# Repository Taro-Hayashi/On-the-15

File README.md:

# On the 15 ビルドガイド（[English](README_EN.md)）
- [キット内容](#キット内容)
- [レイアウトを決める](#レイアウトを決める)
- [はんだ付け](#はんだ付け)
- [組み立て](#組み立て)
- [キーのカスタマイズ](#キーのカスタマイズ)
- [そのほか](#そのほか)

## キット内容

||部品名|数|
|-|-|-|
|1|メインボード|1|
|2|トッププレート|1|
|3|ボトムプレート|1|
|4|ネジ|22|
|5|スペーサー|11|
|6|リセットスイッチ|1|
|7|Cherry MX ホットスワップソケット|60|
|8|ゴム足|6|
|9|アクリルミドルプレート||
|10|2Uスタビライザー|1|
|11|ロータリーエンコーダー|1|
|12|ノブ|1|

### キット以外に必要なもの
|部品名|数|||
|-|-|-|-|
|キースイッチ|〜60|CherryMX互換|[遊舎工房](https://shop.yushakobo.jp/collections/all-switches/cherry-mx-%E4%BA%92%E6%8F%9B-%E3%82%B9%E3%82%A4%E3%83%83%E3%83%81) / [TALPKEYBOARD](https://talpkeyboard.net/?category_id=59cf8860ed05e668db003f5d) / [DailyCraftKeyboard](https://shop.dailycraft.jp/collections/mx-switches)|
|キーキャップ|〜60|CherryMX互換|[遊舎工房](https://shop.yushakobo.jp/collections/keycaps/cherry-mx-%E4%BA%92%E6%8F%9B-%E3%82%AD%E3%83%BC%E3%82%AD%E3%83%A3%E3%83%83%E3%83%97) / [TALPKEYBOARD](https://talpkeyboard.net/?category_id=59e2acfaed05e644fd004008)|
|Type-C ケーブル|1|||

### 追加できるもの
|部品名|||
|-|-|-|
|色違いアクリルプレート|-|[遊舎工房 - キーボードアクリルプレート](https://shop.yushakobo.jp/collections/services/products/keyboard_acrylic_plate?variant=43949129629927)|
|スタビライザー|2U、PCBマウント|[遊舎工房](https://shop.yushakobo.jp/collections/all-keyboard-parts/Stabilizer) / [TALPKEYBOARD](https://talpkeyboard.net/?category_id=5f884b9b3313d216eb50558a)|
|ロータリーエンコーダ|EC11/EC12/ロープロファイル|[遊舎工房](https://shop.yushakobo.jp/search?q=%E3%83%AD%E3%83%BC%E3%82%BF%E3%83%AA%E3%83%BC%E3%82%A8%E3%83%B3%E3%82%B3%E3%83%BC%E3%83%80%E3%83%BC+%E3%83%8E%E3%83%96%E4%BB%98%E3%81%8D) / [TALPKEYBOARD](https://talpkeyboard.net/items/5f3f1a597df28129f2fd4b0f) / [DailyCraftKeyboard](https://shop.dailycraft.jp/products/encoder_low)|
|ノブ|外径19mmまで|[遊舎工房](https://shop.yushakobo.jp/products/3733) / [DailyCraftKeyboard](https://shop.dailycraft.jp/products/encoder_lowprofile_knob)|

専用のアクリルケースもあります。  
- [アクリルケースデータ](acrylic-case/README.md)
  - [fully-acrylic](acrylic-case/fully-acrylic/README.md)
  - [pcb-switchplate](acrylic-case/pcb-switchplate/README.md)

### 必要な工具
|工具名|
|-|
|はんだごて|
|こて先クリーナー（こて台）|
|鉛入りはんだ|
|ピンセット|
|精密ドライバー|

## レイアウトを決める
On the 15は60キーの格子配列キーボードですが、色のついたキーは長さを変更することができます。  

ビルドガイドではこのようなレイアウトで組み立てます。　

## はんだ付け
### ソケットのはんだ付け
使うソケットのパッドに予備はんだをします。  
あらかじめ薄くはんだを乗せます。  
  
ソケットを置いたらピンセットで押さえつけながらはんだを注いでいきます。入り組んでいて表面積が多いので多めに必要になります。

慣れてきたら予備はんだを省略したり、一度に複数個置いてはんだ付けをすると楽になります。  
  
### リセットスイッチのはんだ付け
表面左側のRESETと書いてあるところにリセットスイッチを差して裏からはんだ付けします。  

### ロータリーエンコーダーのはんだ付け
足を折らないようにホールに通して裏からはんだ付けします。  

### テストファームウェアの書き込み
テスト用のファームウェアをこちらからダウンロードしてください。
- https://remap-keys.app/catalog/9bQPDxdkX8xgflHlsR9p/firmware

QMK Toolboxのreleaseページから最新版をダウンロードしてインストールください。  
- [Releases・qmk/qmk_toolbox](https://github.com/qmk/qmk_toolbox/releases)

起動したらOpenを押してダウンロードしたファームウェアを指定し、はんだ付けしたリセットボタンを押します。  
   
新しく黄色の文字が出てきたらFlashを押します。  

Thank youの後に黄色い文字が出たら更新完了です。  

### 動作確認
キースイッチを差したり裏をピンセットで短絡したりして動作確認をします。  

## 組み立て
### スタビライザーを組み立てる
スタビライザーがあると2Uのキーの押下が安定します。無くても使えるのでお好みでお使いください。  
ねじ止め式のスタビライザーは縦に二つ並べておくことはできないので使う場所に気をつけるかスナップ型のスタビライザーを使ってください。  

小さい方のパーツの穴が二つ開いている側を、大きいパーツの穴が開いている方向に合わせて組み合わせます。  
  
金属の棒を下の穴に差し込みツメにパチっと音がするまで押し込んで完成です。  
    
基板の大きい方の穴にツメをひっかけながら取り付けます。  

### メインボードにトッププレートを取り付ける
トッププレートの裏側にスペーサーをねじ止めします。  
   
メインボードにかぶせて、4隅のスイッチをはめ込みます。  
   
すべてのスイッチを差し込みました。  

### アクリルプレートを挟み込む
画像のような形で3段にして挟み込みます。  

### バックプレートを取り付ける
バックプレートをねじ止めしてゴム足を貼ります。  
  
キーキャップを付けたら完成です。  

### Remap用ファームウェアの書き込み
Remap用のファームウェアをこちらからダウンロードして、さきほどと同様に書き込んでください。
- https://remap-keys.app/catalog/9bQPDxdkX8xgflHlsR9p/firmware

## キーのカスタマイズ
こちらのサイトにアクセスしてください。
- Remap https://remap-keys.app

左を選んで進んでいくとダイアログが出てキーボードを選択できます。  
  
選択して接続してください。

### キーマップの保存と復元
⇔アイコンで作ったキーマップを保存することができます。  
  
作ったキーマップを共有することもできるので是非お試しください。

### レイアウトを変える
キーボードの右のこのボタンでレイアウトを変えることができます。  

### キーを設定する
下のキー一覧からドラッグアンドドロップし、変更が終わったら右上のflashボタンを押すと反映されます。  
  
また、USキーボードとJISキーボードはFlashの下のプルダウンから変更できます。OSの設定に合わせてください。

### 修飾キーとの組み合わせを設定する
上のキーボードのキーをクリックすると設定画面になります。
  
修飾キーと同時押ししたいキーを検索し、同時押ししたい修飾キーにチェックを入れます。

Hold-Tapもここから設定できます。

### ロータリーエンコーダーを設定する
丸いキーの左下をクリックすると時計回り、反時計回りを切り替えることができるので、それぞれにキーを割り当てます。

### 特殊なキーを設定する
FUNCTIONSタブのVIA USER KEYにあらかじめ用意されたショートカットキーがあります。

### LEDを調整する
このボタンで発光方法を変更することができます。

## そのほか
### リセットスイッチの押し方
こちらの隙間からドライバーやピンセットを差し込むことで押すことができます。

### ファームウェアのコード
https://github.com/Taro-Hayashi/qmk_firmware/tree/tarohayashi/keyboards/tarohayashi/onthe15

### プレートのデータ
- [onthe15_plates.zip](https://github.com/Taro-Hayashi/On-the-15/releases/download/0.22.3/onthe15_plates.zip)

### アクリルケースのデータ
- [fully-acrylic](acrylic-case/fully-acrylic/README.md)
- [pcb-switchplate](acrylic-case/pcb-switchplate/README.md)

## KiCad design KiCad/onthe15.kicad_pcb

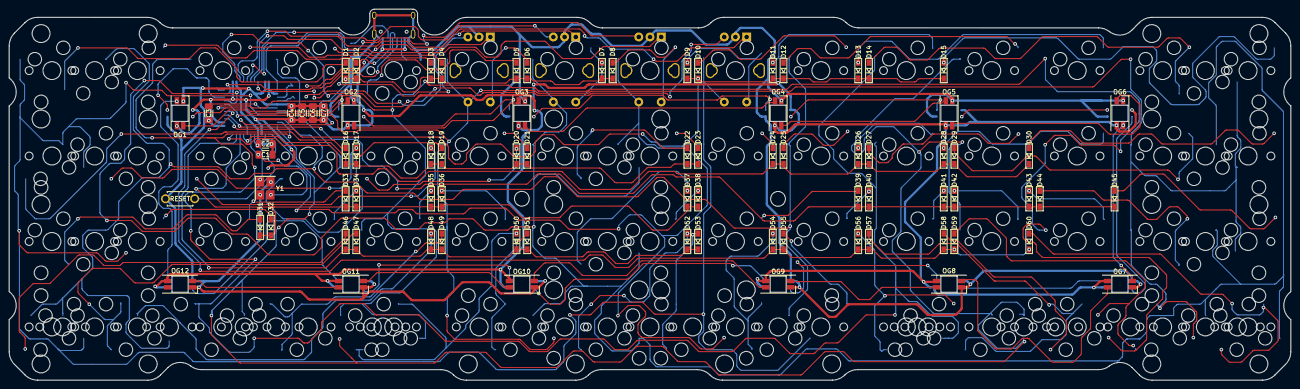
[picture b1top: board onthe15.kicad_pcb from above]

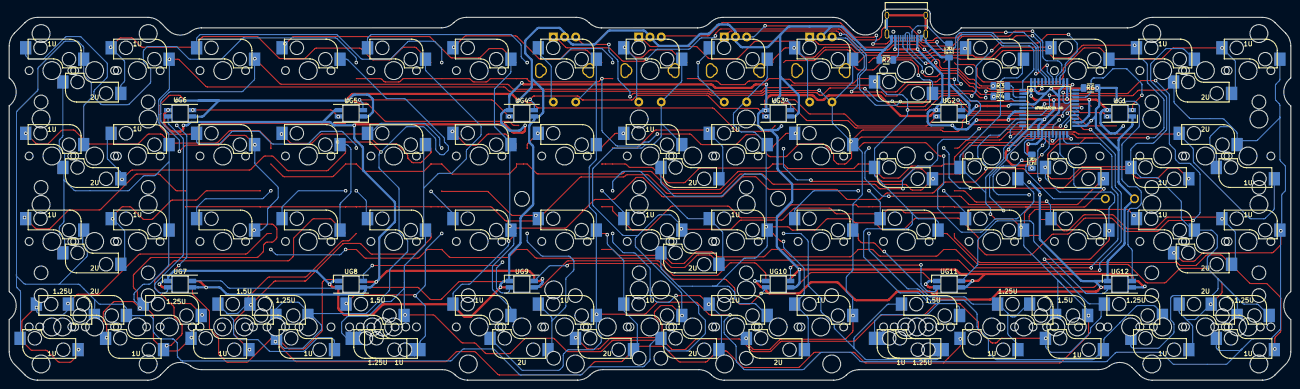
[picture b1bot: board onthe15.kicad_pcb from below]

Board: 2 copper layers, 285.8 x 82.7 mm, 193 parts (20 on the bottom side), 121 nets.

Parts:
C1, C2: 22p; C_1206_3216_SMD
C3: 1u; C_1206_3216_SMD
C4, C5, C6: 0.1u; C_1206_3216_SMD
C7: 10u; C_1206_3216_SMD
D1, D2, D3, D4, D5, D6, D7, D8, D9, D10, D11, D12, D13, D14, D15, D16, D17, D18, D19, D20, D21, D22, D23, D24, D25, D26, D27, D28, D29, D30, D31, D32, D33, D34, D35, D36, D37, D38, D39, D40, D41, D42, D43, D44, D45, D46, D47, D48, D49, D50, D51, D52, D53, D54, D55, D56, D57, D58, D59, D60: D; Diode_SMD
H5, H6: Hole; Hole_3.3mm_Spacer
J1: USB_C_Receptacle_USB2.0
OG1, OG2, OG3, OG4, OG5, OG6, OG7, OG8, OG9, OG10, OG11, OG12: YS-SK6812MINI-E_overglow; YS-SK6812MINI-E_Undergrow_NOHOLE
R1, R2: 5.1k; R_1206_3216_SMD
R3, R4: 22; R_1206_3216_SMD
R5, R6: 10k; R_1206_3216_SMD
RE1, RE2, RE3, RE4: Rotary_Encoder; RotaryEncoder
RST1: ResetSW
SW1, SW2, SW19, SW20, SW36, SW37, SW38, SW62, SW66, SW67, SW71: 2U; MXOnly-2U-FLIPPED-Hotswap-LED
SW3, SW4, SW16, SW17, SW21, SW22, SW27, SW28, SW34, SW35, SW39, SW40, SW45, SW46, SW52, SW53, SW72, SW73, SW74, SW75, SW76, SW77, SW78, SW79, SW80, SW81, SW82, SW83, SW84, SW85, SW86: 1U; MXOnly-1U-Hotswap
SW5, SW6, SW7, SW8, SW9, SW10, SW11, SW12, SW13, SW14, SW15, SW23, SW24, SW25, SW26, SW29, SW30, SW31, SW32, SW33, SW41, SW42, SW43, SW44, SW47, SW48, SW49, SW50, SW51: SW_PUSH; MXOnly-1U-Hotswap
SW18, SW65, SW68: 2U; MXOnly-2U-Hotswap-ReversedStabilizers
SW54, SW56, SW57, SW58, SW59, SW61: 1.25U; MXOnly-1.25U-Hotswap
SW55, SW60: 1.25U; MXOnly-1.25U-Hotswap-Reverse
SW63, SW64, SW69, SW70: 1.5U; MXOnly-1.5U-Hotswap
U1: ATMEGA32U4-AU
UG1, UG2, UG3, UG4, UG5, UG6, UG7, UG8, UG9, UG10, UG11, UG12: YS-SK6812MINI-E_underglow; YS-SK6812MINI-E_Undergrow
Y1: Crystal; Crystal_3225_SMD

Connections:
GND: C1.2, C2.2, C3.2, C4.2, C5.2, C6.2, C7.2, J1.A1 (GND), J1.A12 (GND), J1.B1 (GND), J1.B12 (GND), J1.S1 (SHIELD), OG1.3 (VSS), OG2.3 (VSS), OG3.3 (VSS), OG4.3 (VSS), OG5.3 (VSS), OG6.3 (VSS), OG7.3 (VSS), OG8.3 (VSS), OG9.3 (VSS), OG10.3 (VSS), OG11.3 (VSS), OG12.3 (VSS), R1.2, R2.2, R6.2, RE1.C, RE2.C, RE3.C, RE4.C, RST1.2, U1.5 (UGND), U1.15 (GND), U1.23 (GND), U1.35 (GND), U1.43 (GND), UG1.3 (VSS), UG2.3 (VSS), UG3.3 (VSS), UG4.3 (VSS), UG5.3 (VSS), UG6.3 (VSS), UG7.3 (VSS), UG8.3 (VSS), UG9.3 (VSS), UG10.3 (VSS), UG11.3 (VSS), UG12.3 (VSS), Y1.2, Y1.4
unnamed: C3.1, U1.6 (UCAP)
unnamed: D1.2 (A), SW1.2, SW3.2
unnamed: D2.2 (A), SW4.2
unnamed: D3.2 (A), SW5.2
unnamed: D4.2 (A), SW6.2
unnamed: D5.2 (A), SW7.2
unnamed: D10.2 (A), SW12.2
unnamed: D11.2 (A), SW13.2
unnamed: D12.2 (A), SW14.2
unnamed: D13.2 (A), SW15.2
unnamed: D14.2 (A), SW2.2, SW16.2
unnamed: D15.2 (A), SW17.2
unnamed: D16.2 (A), SW18.2, SW21.2
unnamed: D17.2 (A), SW22.2
unnamed: D18.2 (A), SW23.2
unnamed: D19.2 (A), SW24.2
unnamed: D20.2 (A), SW25.2
unnamed: D21.2 (A), SW26.2
unnamed: D22.2 (A), SW19.2, SW27.2
unnamed: D23.2 (A), SW28.2
unnamed: D24.2 (A), SW29.2
unnamed: D25.2 (A), SW30.2
unnamed: D26.2 (A), SW31.2
unnamed: D27.2 (A), SW32.2
unnamed: D28.2 (A), SW33.2
unnamed: D29.2 (A), SW20.2, SW34.2
unnamed: D30.2 (A), SW35.2
unnamed: D31.2 (A), SW36.2, SW39.2
unnamed: D32.2 (A), SW40.2
unnamed: D33.2 (A), SW41.2
unnamed: D34.2 (A), SW42.2
unnamed: D35.2 (A), SW43.2
unnamed: D36.2 (A), SW44.2
unnamed: D37.2 (A), SW37.2, SW45.2
unnamed: D38.2 (A), SW46.2
unnamed: D39.2 (A), SW47.2
unnamed: D40.2 (A), SW48.2
unnamed: D41.2 (A), SW49.2
unnamed: D42.2 (A), SW50.2
unnamed: D43.2 (A), SW51.2
unnamed: D44.2 (A), SW38.2, SW52.2
unnamed: D45.2 (A), SW53.2
unnamed: D46.2 (A), SW72.2
unnamed: D47.2 (A), SW54.2, SW62.2, SW73.2
unnamed: D48.2 (A), SW55.2, SW74.2
unnamed: D49.2 (A), SW56.2, SW63.2, SW75.2
unnamed: D50.2 (A), SW57.2, SW64.2, SW76.2
unnamed: D51.2 (A), SW65.2, SW77.2
unnamed: D52.2 (A), SW66.2, SW78.2
unnamed: D53.2 (A), SW67.2, SW79.2
unnamed: D54.2 (A), SW68.2, SW80.2
unnamed: D55.2 (A), SW81.2
unnamed: D56.2 (A), SW58.2, SW69.2, SW82.2
unnamed: D57.2 (A), SW59.2, SW70.2, SW83.2
unnamed: D58.2 (A), SW84.2
unnamed: D59.2 (A), SW60.2, SW85.2
unnamed: D60.2 (A), SW61.2, SW71.2, SW86.2
unnamed: J1.A5 (CC1), R1.1
unnamed: J1.A6 (D+), J1.B6 (D+), R4.2
unnamed: J1.A7 (D-), J1.B7 (D-), R3.2
unnamed: J1.B5 (CC2), R2.1
unnamed: OG1.2 (DOUT), OG2.4 (DIN)
unnamed: OG1.4 (DIN), UG12.2 (DOUT)
unnamed: OG2.2 (DOUT), OG3.4 (DIN)
unnamed: OG3.2 (DOUT), OG4.4 (DIN)
unnamed: OG4.2 (DOUT), OG5.4 (DIN)
unnamed: OG5.2 (DOUT), OG6.4 (DIN)
unnamed: OG6.2 (DOUT), OG7.4 (DIN)
unnamed: OG7.2 (DOUT), OG8.4 (DIN)
unnamed: OG8.2 (DOUT), OG9.4 (DIN)
unnamed: OG10.2 (DOUT), OG11.4 (DIN)
unnamed: OG9.2 (DOUT), OG10.4 (DIN)
unnamed: OG11.2 (DOUT), OG12.4 (DIN)
unnamed: R6.1, U1.33 (PE2)
unnamed: UG1.2 (DOUT), UG2.4 (DIN)
unnamed: UG2.2 (DOUT), UG3.4 (DIN)
unnamed: UG3.2 (DOUT), UG4.4 (DIN)
unnamed: UG4.2 (DOUT), UG5.4 (DIN)
unnamed: UG5.2 (DOUT), UG6.4 (DIN)
unnamed: UG6.2 (DOUT), UG7.4 (DIN)
unnamed: UG7.2 (DOUT), UG8.4 (DIN)
unnamed: UG8.2 (DOUT), UG9.4 (DIN)
unnamed: UG10.2 (DOUT), UG11.4 (DIN)
unnamed: UG9.2 (DOUT), UG10.4 (DIN)
unnamed: UG11.2 (DOUT), UG12.4 (DIN)
VCC: C4.1, C5.1, C6.1, C7.1, J1.A4 (VBUS), J1.A9 (VBUS), J1.B4 (VBUS), J1.B9 (VBUS), OG1.1 (VDD), OG2.1 (VDD), OG3.1 (VDD), OG4.1 (VDD), OG5.1 (VDD), OG6.1 (VDD), OG7.1 (VDD), OG8.1 (VDD), OG9.1 (VDD), OG10.1 (VDD), OG11.1 (VDD), OG12.1 (VDD), R5.2, U1.2 (UVCC), U1.7 (VBUS), U1.14 (VCC), U1.24 (AVCC), U1.34 (VCC), U1.44 (AVCC), UG1.1 (VDD), UG2.1 (VDD), UG3.1 (VDD), UG4.1 (VDD), UG5.1 (VDD), UG6.1 (VDD), UG7.1 (VDD), UG8.1 (VDD), UG9.1 (VDD), UG10.1 (VDD), UG11.1 (VDD), UG12.1 (VDD)
col0: RE4.S1, SW1.1, SW3.1, SW11.1, SW18.1, SW21.1, SW29.1, SW36.1, SW39.1, SW47.1, SW68.1, SW72.1, SW80.1, U1.8 (PB0)
col1: SW4.1, SW12.1, SW22.1, SW30.1, SW40.1, SW48.1, SW54.1, SW62.1, SW73.1, SW81.1, U1.9 (PB1)
col2: SW5.1, SW13.1, SW23.1, SW31.1, SW41.1, SW49.1, SW55.1, SW58.1, SW69.1, SW74.1, SW82.1, U1.10 (PB2)
col3: SW6.1, SW14.1, SW24.1, SW32.1, SW42.1, SW50.1, SW56.1, SW59.1, SW63.1, SW70.1, SW75.1, SW83.1, U1.11 (PB3)
col4: SW7.1, SW15.1, SW25.1, SW33.1, SW43.1, SW51.1, SW57.1, SW64.1, SW76.1, SW84.1, U1.28 (PB4)
col5: RE1.S1, SW2.1, SW8.1, SW16.1, SW20.1, SW26.1, SW34.1, SW38.1, SW44.1, SW52.1, SW60.1, SW65.1, SW77.1, SW85.1, U1.29 (PB5)
col6: RE2.S1, SW9.1, SW17.1, SW19.1, SW27.1, SW35.1, SW37.1, SW45.1, SW53.1, SW61.1, SW66.1, SW71.1, SW78.1, SW86.1, U1.30 (PB6)
col7: RE3.S1, SW10.1, SW28.1, SW46.1, SW67.1, SW79.1, U1.12 (PB7)
d+: R4.1, U1.4 (D+)
d-: R3.1, U1.3 (D-)
led: U1.31 (PC6), UG1.4 (DIN)
reset: R5.1, RST1.1, U1.13 (~RESET)
rot1a: RE1.A, U1.32 (PC7)
rot1b: RE1.B, U1.1 (PE6)
rot1s2: D6.2 (A), RE1.S2, SW8.2
rot2a: RE2.A, U1.41 (PF0)
rot2b: RE2.B, U1.40 (PF1)
rot2s2: D7.2 (A), RE2.S2, SW9.2
rot3a: RE3.A, U1.39 (PF4)
rot3b: RE3.B, U1.38 (PF5)
rot3s2: D8.2 (A), RE3.S2, SW10.2
rot4a: RE4.A, U1.37 (PF6)
rot4b: RE4.B, U1.36 (PF7)
rot4s2: D9.2 (A), RE4.S2, SW11.2
row0: D1.1 (K), D2.1 (K), D3.1 (K), D4.1 (K), D5.1 (K), D6.1 (K), D7.1 (K), D8.1 (K), U1.18 (PD0)
row1: D16.1 (K), D17.1 (K), D18.1 (K), D19.1 (K), D20.1 (K), D21.1 (K), D22.1 (K), D23.1 (K), U1.19 (PD1)
row2: D31.1 (K), D32.1 (K), D33.1 (K), D34.1 (K), D35.1 (K), D36.1 (K), D37.1 (K), D38.1 (K), U1.20 (PD2)
row3: D46.1 (K), D47.1 (K), D48.1 (K), D49.1 (K), D50.1 (K), D51.1 (K), D52.1 (K), D53.1 (K), U1.21 (PD3)
row4: D9.1 (K), D10.1 (K), D11.1 (K), D12.1 (K), D13.1 (K), D14.1 (K), D15.1 (K), U1.25 (PD4)
row5: D24.1 (K), D25.1 (K), D26.1 (K), D27.1 (K), D28.1 (K), D29.1 (K), D30.1 (K), U1.22 (PD5)
row6: D39.1 (K), D40.1 (K), D41.1 (K), D42.1 (K), D43.1 (K), D44.1 (K), D45.1 (K), U1.26 (PD6)
row7: D54.1 (K), D55.1 (K), D56.1 (K), D57.1 (K), D58.1 (K), D59.1 (K), D60.1 (K), U1.27 (PD7)
xtal1: C1.1, U1.17 (XTAL1), Y1.3
xtal2: C2.1, U1.16 (XTAL2), Y1.1

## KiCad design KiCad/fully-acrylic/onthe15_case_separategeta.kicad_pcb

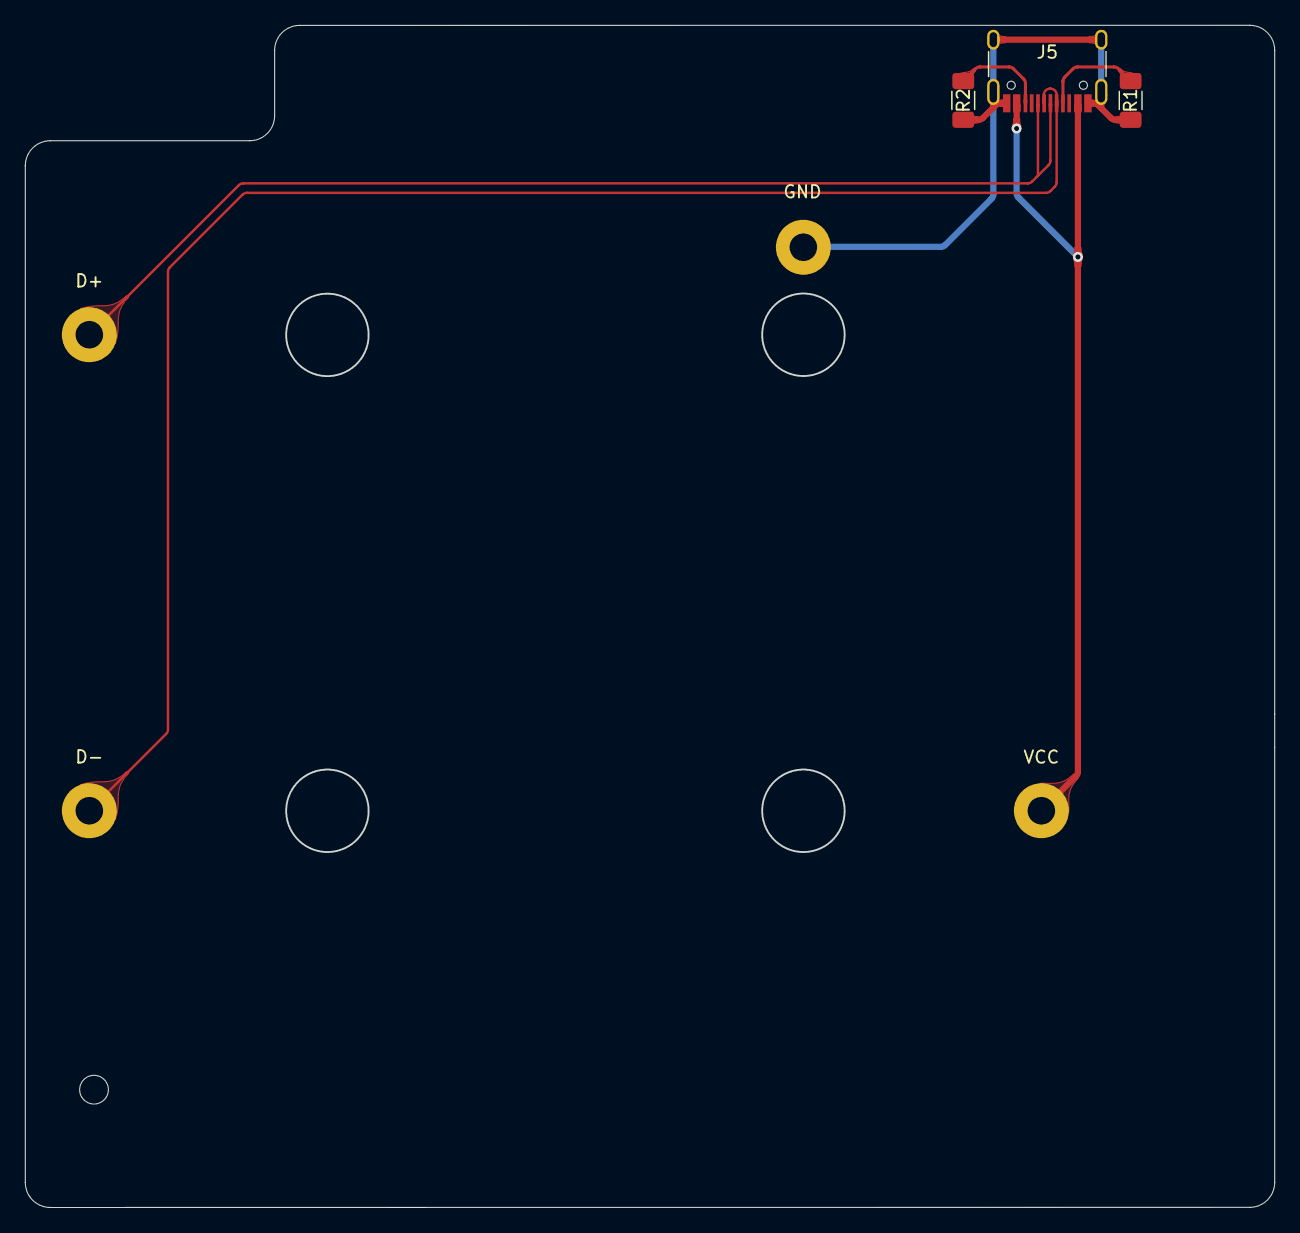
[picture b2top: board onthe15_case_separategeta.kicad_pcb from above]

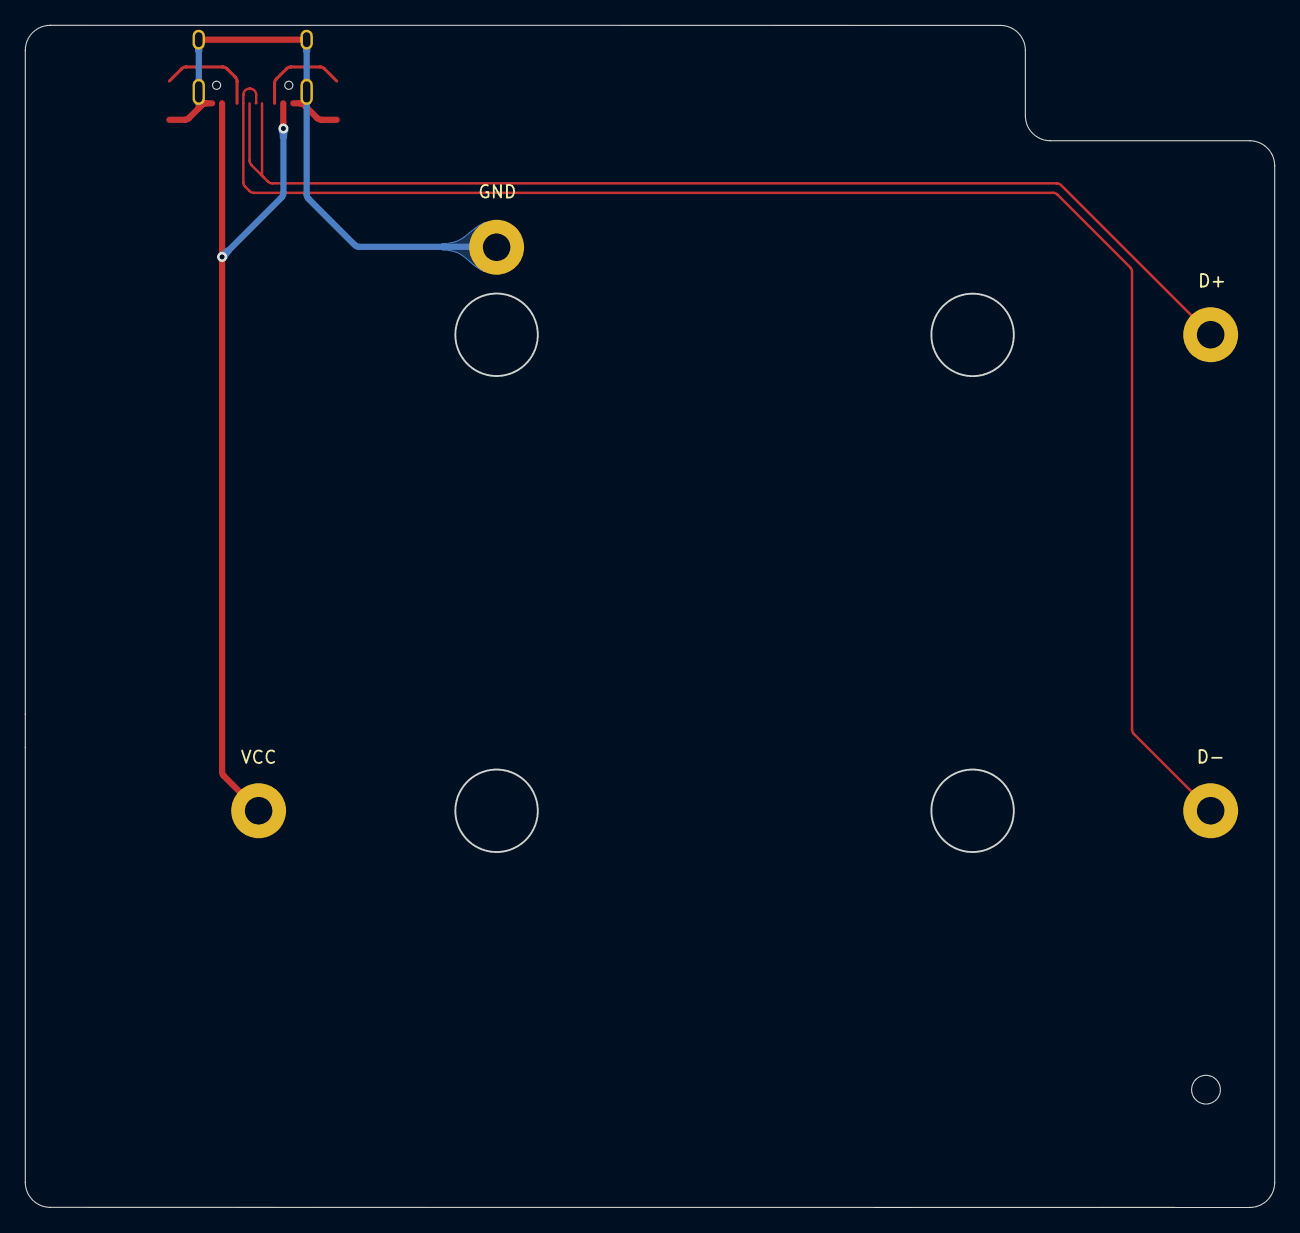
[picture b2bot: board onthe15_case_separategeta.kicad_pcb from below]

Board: 2 copper layers, 100.0 x 94.6 mm, 10 parts (6 on the bottom side), 6 nets.

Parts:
HOLE1, HOLE1#2, HOLE4: Hole_5x2.3_6; Hole_5x2.5_7
J1, J2, J3, J4: Conn_01x01_Female; Conn_2.2mm_M2
J5: USB_C_Receptacle_USB2.0
R1, R2: 5.1k; R_1206_3216_SMD

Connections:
D+: J4.1, J5.A6 (D+), J5.B6 (D+)
D-: J3.1, J5.A7 (D-), J5.B7 (D-)
GND: J2.1, J5.A1 (GND), J5.A12 (GND), J5.B1 (GND), J5.B12 (GND), J5.S1 (SHIELD), R1.2, R2.2
unnamed: J5.A5 (CC1), R1.1
unnamed: J5.B5 (CC2), R2.1
VCC: J1.1, J5.A4 (VBUS), J5.A9 (VBUS), J5.B4 (VBUS), J5.B9 (VBUS)

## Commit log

2022-03-20 text
2022-06-28 Rename README_SA.md to README_EN.md
2023-08-09 0.21.6
2026-05-24 Add hardware and acrylic case files
